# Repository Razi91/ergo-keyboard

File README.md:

# ErgoDox+
Ergo mechanical split keyboard based on ErgoDox layout with vertical encoder and Cirque GlidePoint trackpad

Open with KiCad

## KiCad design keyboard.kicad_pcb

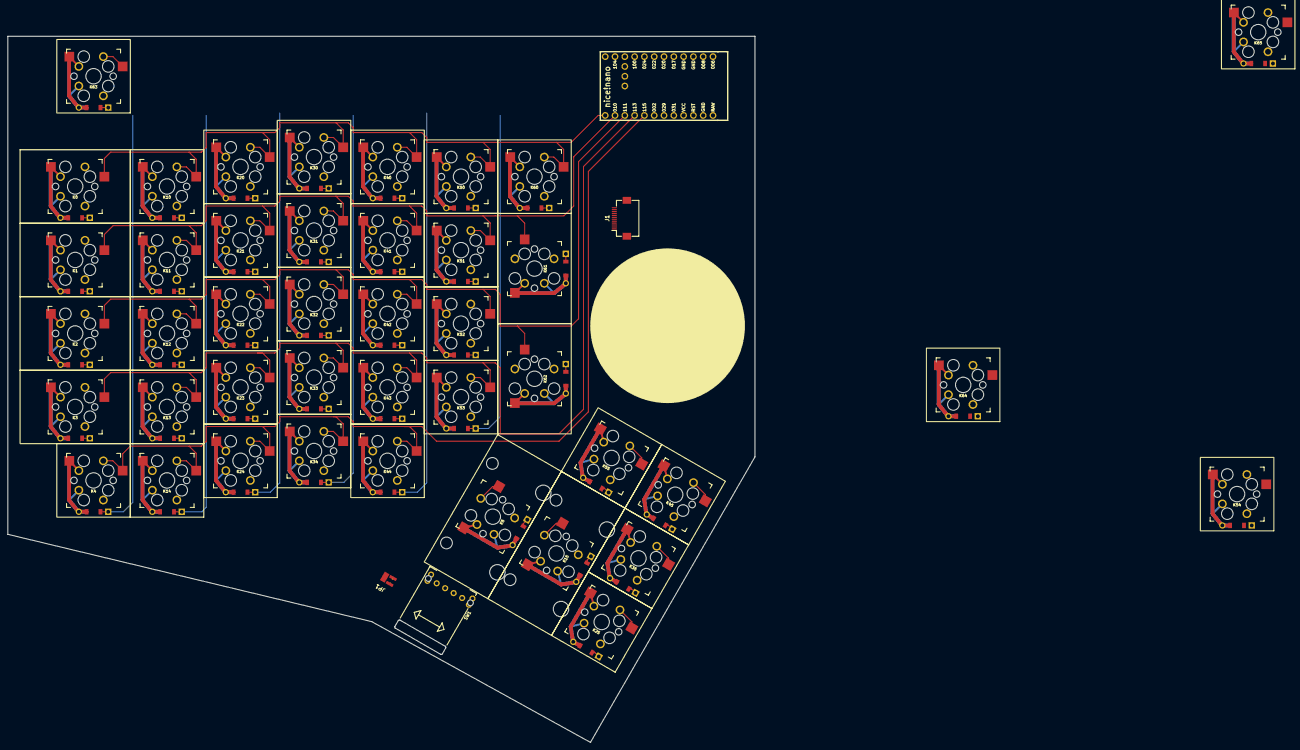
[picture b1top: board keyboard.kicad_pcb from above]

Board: 2 copper layers, 193.7 x 183.0 mm, 46 parts (0 on the bottom side), 22 nets.

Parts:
J1: Cirque_GlidePoint; Hirose_FH12-12S-0.5SH_1x12-1MP_P0.50mm_Horizontal
JP1: solder_switch
K0, K1, K2, K3, K61, K62: SWITCH_DIODE_1-5U; kailh_socket_1-5U
K4, K10, K11, K12, K13, K14, K20, K21, K22, K23, K24, K25, K30, K31, K32, K33, K34, K35, K40, K41, K42, K43, K44, K45, K50, K51, K52, K53, K54, K55, K60, K63, K64, K65: SWITCH_DIODE; kailh_socket_1U
K5, K15: SWITCH_DIODE_2U; kailh_socket_2U
SW1: evqwdg001; evqwdg001_sym
U1: nice_nano

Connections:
+3V3: J1.12 (VDD), U1.21 (VCC)
ENC_A: SW1.A, SW1.D, U1.19 (AIN5/P0.29)
ENC_B: JP1.3 (OUTA), U1.20 (AIN7/P0.31)
GND: J1.11 (GND), JP1.4 (OUTB), U1.3 (GND), U1.4 (GND), U1.23 (GND)
unnamed: JP1.1 (IN1), SW1.C
unnamed: JP1.2 (IN2), SW1.B
SCL: J1.9 (SCL), U1.2 (RX1/P0.08)
SDA: J1.10 (SDA), U1.1 (TX0/P0.06)
TP_DR: J1.4 (DR), U1.31 (P1.01)
col0: K0.4 (K), K1.4 (K), K2.4 (K), K3.4 (K), K4.4 (K), K5.4 (K), U1.6 (P0.20)
col1: K10.4 (K), K11.4 (K), K12.4 (K), K13.4 (K), K14.4 (K), K15.4 (K), U1.7 (P0.22)
col2: K20.4 (K), K21.4 (K), K22.4 (K), K23.4 (K), K24.4 (K), K25.4 (K), U1.8 (P0.24)
col3: K30.4 (K), K31.4 (K), K32.4 (K), K33.4 (K), K34.4 (K), K35.4 (K), U1.9 (P1.00)
col4: K40.4 (K), K41.4 (K), K42.4 (K), K43.4 (K), K44.4 (K), K45.4 (K), U1.10 (P0.11)
col5: K50.4 (K), K51.4 (K), K52.4 (K), K53.4 (K), K54.4 (K), K55.4 (K), SW1.S2, U1.11 (P1.04)
col6: K60.4 (K), K61.4 (K), K62.4 (K), K63.4 (K), K64.4 (K), K65.4 (K), U1.12 (P1.06)
row0: K0.1, K10.1, K20.1, K30.1, K40.1, K50.1, K60.1, U1.13 (NFC1/P0.09)
row1: K1.1, K11.1, K21.1, K31.1, K41.1, K51.1, K61.1, U1.14 (NFC2/P0.10)
row2: K2.1, K12.1, K22.1, K32.1, K42.1, K52.1, K62.1, U1.15 (P1.11)
row3: K3.1, K13.1, K23.1, K33.1, K43.1, K53.1, K63.1, U1.16 (P1.13)
row4: K4.1, K14.1, K24.1, K34.1, K44.1, K54.1, K64.1, SW1.S1, U1.17 (P1.15)
row5: K5.1, K15.1, K25.1, K35.1, K45.1, K55.1, K65.1, U1.18 (AIN0/P0.02)

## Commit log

2023-01-22 init
2023-01-23 progress
2023-01-23 readme + routes
